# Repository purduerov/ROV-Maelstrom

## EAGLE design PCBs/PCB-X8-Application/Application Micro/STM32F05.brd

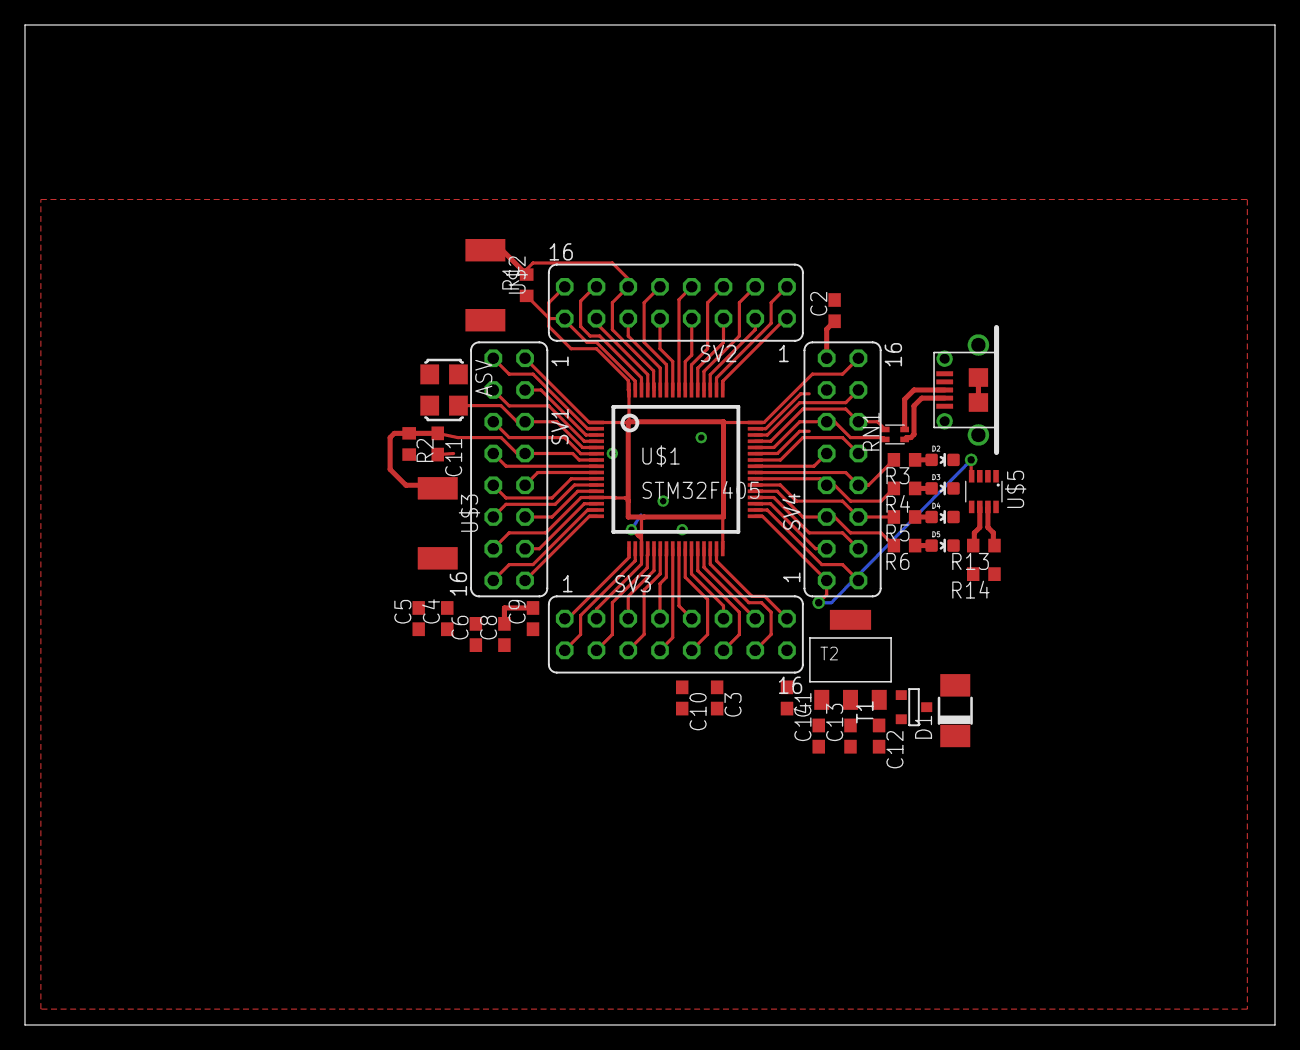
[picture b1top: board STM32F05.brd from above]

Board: 2 copper layers, 100.0 x 80.0 mm, 40 parts (1 on the bottom side), 67 nets.

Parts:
ASV: 8.000MHZ; ASF
C1, C2: 2.2uF; C0603
C3, C4, C5, C6, C9, C11, C13: 0.1uF; C0603
C7: 10nF; C0603
C8: 4.7uF; C0603
C10: 1uF; C0603
C12, C14: 0.22uF; C0603
D1: DO-214AC
D2: Yellow; LED-0603
D3: RED; LED-0603
D4: BLUE; LED-0603
D5: GREEN; LED-0603
R1, R2: 10K; R0603
R3, R4, R6: 82; R0603
R5: 10; R0603
R13: 120; R0603
R14: 100K; R0603
RN1: EXBV4V
SV1: Left; FE08-2
SV2: Top; FE08-2
SV3: Bottom; FE08-2
SV4: Right; FE08-2
T1: FDN340P; SOT-23
T2: AP1117_LIN_REG; SOT223
U$1: STM32F405; LQFP64
U$2, U$3: SWITCH; SW_2512
U$4: MICROUSB; MICRO_B
U$5: MAX3051MAX3051; SOT23-8L

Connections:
+3V3: ASV.4, C3.1, C4.1, C5.1, C6.1, C7.1, C8.1, C9.1, C10.1, C13.1, C14.1, R2.2, SV1.1, SV1.14, SV2.16, SV3.3, SV3.16, SV4.16, T2.TAB, T2.VOUT, U$1.1, U$1.13, U$1.19, U$1.32, U$1.48, U$1.64, U$2.2, U$5.3
+5V: D1.A, T1.3
BOOT0: R1.2, SV2.12, U$1.60, U$2.1
CAM_LED: SV3.6, U$1.22
CAN2_RX: SV4.1, U$1.33, U$5.4
CAN2_TX: SV4.2, U$1.34, U$5.1
CANH: R13.1, U$5.7
CANL: R13.2, U$5.6
DBUG_LED1: R3.2, SV4.8, U$1.40
DBUG_LED2: R4.2, SV4.7, U$1.39
DBUG_LED3: R5.2, SV4.6, U$1.38
DBUG_LED4: R6.2, SV4.5, U$1.37
GND: ASV.2, C1.2, C2.2, C3.2, C4.2, C5.2, C6.2, C7.2, C8.2, C9.2, C10.2, C11.2, C12.2, C13.2, C14.2, D2.C, D3.C, D4.C, D5.C, R1.1, R14.2, SV1.11, SV2.15, SV3.2, SV3.12, T2.GND, U$1.12, U$1.18, U$1.28, U$1.63, U$3.2, U$4.GND1, U$4.GND2, U$4.GND3, U$4.GND4, U$4.GND7, U$4.GND8, U$4.P4, U$4.P5, U$5.2
unnamed: RN1.1, U$4.P2
unnamed: RN1.2, U$4.P3
unnamed: T1.1, U$4.P1
unnamed: C12.1, D1.C, T1.2, T2.VIN
unnamed: D2.A, R3.1
unnamed: D3.A, R4.1
unnamed: D4.A, R5.1
unnamed: D5.A, R6.1
unnamed: R14.1, U$5.8
NRST: C11.1, R2.1, SV1.7, U$1.7, U$3.1
OSCIN: ASV.3, SV1.5, U$1.5
OSCOUT: SV1.6, U$1.6
PIN2: SV1.2, U$1.2
PIN3: SV1.3, U$1.3
PIN4: SV1.4, U$1.4
PIN11: SV1.12, U$1.11
PIN14: SV1.13, U$1.14
PIN15: SV1.16, U$1.15
PIN16: SV1.15, U$1.16
PIN17: SV3.1, U$1.17
PIN20: SV3.4, U$1.20
PIN21: SV3.5, U$1.21
PIN23: SV3.7, U$1.23
PIN24: SV3.8, U$1.24
PIN25: SV3.9, U$1.25
PIN26: SV3.10, U$1.26
PIN27: SV3.11, U$1.27
PIN29: SV3.13, U$1.29
PIN30: SV3.14, U$1.30
PIN35: SV4.3, U$1.35
PIN36: SV4.4, U$1.36
PIN41: SV4.9, U$1.41
PIN42: SV4.10, U$1.42
PIN46: SV4.14, U$1.46
PIN49: SV2.1, U$1.49
PIN50: SV2.2, U$1.50
PIN51: SV2.3, U$1.51
PIN52: SV2.4, U$1.52
PIN53: SV2.5, U$1.53
PIN54: SV2.6, U$1.54
PIN55: SV2.7, U$1.55
PIN56: SV2.8, U$1.56
PIN57: SV2.9, U$1.57
PIN59: SV2.11, U$1.59
PIN61: SV2.13, U$1.61
PIN62: SV2.14, U$1.62
SHFT_REG_CLK: SV1.9, U$1.9
SHFT_REG_DATA: SV1.8, U$1.8
SHFT_REG_EN: SV1.10, U$1.10
TEMP_SENS: SV2.10, U$1.58
USBD+: RN1.3, SV4.12, U$1.45
USBD-: RN1.4, SV4.11, U$1.44
VCAP_1: C1.1, SV3.15, U$1.31
VCAP_2: C2.1, SV4.15, U$1.47

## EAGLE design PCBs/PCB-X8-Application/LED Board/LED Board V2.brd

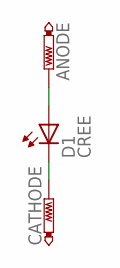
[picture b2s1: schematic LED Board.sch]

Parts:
ANODE: PTR1PAD1-20; P1-20
CATHODE: PTR1PAD1-20; P1-20
D1: CREE; CREE-XLAMP-XM-L

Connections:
ANODE: ANODE.TP, D1.A, D1.A@1 (A)
CATHODE: CATHODE.TP, D1.C, D1.C1 (C), D1.C@1 (C)

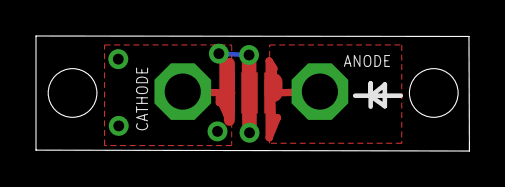
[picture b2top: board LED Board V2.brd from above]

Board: 2 copper layers, 24.1 x 6.4 mm, 3 parts (0 on the bottom side), 2 nets.

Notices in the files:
parts and their libraries:
SparkFun-LED: Licensing: Creative Commons ShareAlike 4.0 International - https://creativecommons.org/licenses/by-sa/4.0
